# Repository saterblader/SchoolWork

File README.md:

School Work
============
This repository contains projects that I have 
worked on as part of my Masters Degree in 
Computer Engineering while at Syracuse University. 
For Hardware designs provided they are most likely 
laid-out in KiCAD 4.0+ and can be opened with that 
software. All code is provided AS IS and some 
code contains bugs that I never had time to fix 
while working on the project for the class. If 
you are a SU student who has found this please 
note that use of this code for school projects 
is a violation of the University Academic 
Integrity policy and could result in a referral 
to the Academic Integrity Review Board. 

Contact Information
--------------------
Philip D. Geramian 
pdgerami@syr.edu

Last Updated
-------------
April 3rd, 2017

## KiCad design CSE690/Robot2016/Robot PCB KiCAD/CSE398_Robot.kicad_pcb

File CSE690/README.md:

CSE-690
======== 
This folder contains my projects from CSE-690 
Spring 2016 an Independent Study at Syracuse 
University where my advisor for the project 
and I wished to design a new robot platform based 
on the NXP-Freescale Kinetis KL05 Platform. 

If you are a SU student who has found this please 
note that use of this code for school projects 
is a violation of the University Academic 
Integrity policy and could result in a referral 
to the Academic Integrity Review Board. 

Contact Information
--------------------
Philip D. Geramian 
pdgerami@syr.edu

Last Updated
-------------
November 20th, 2016

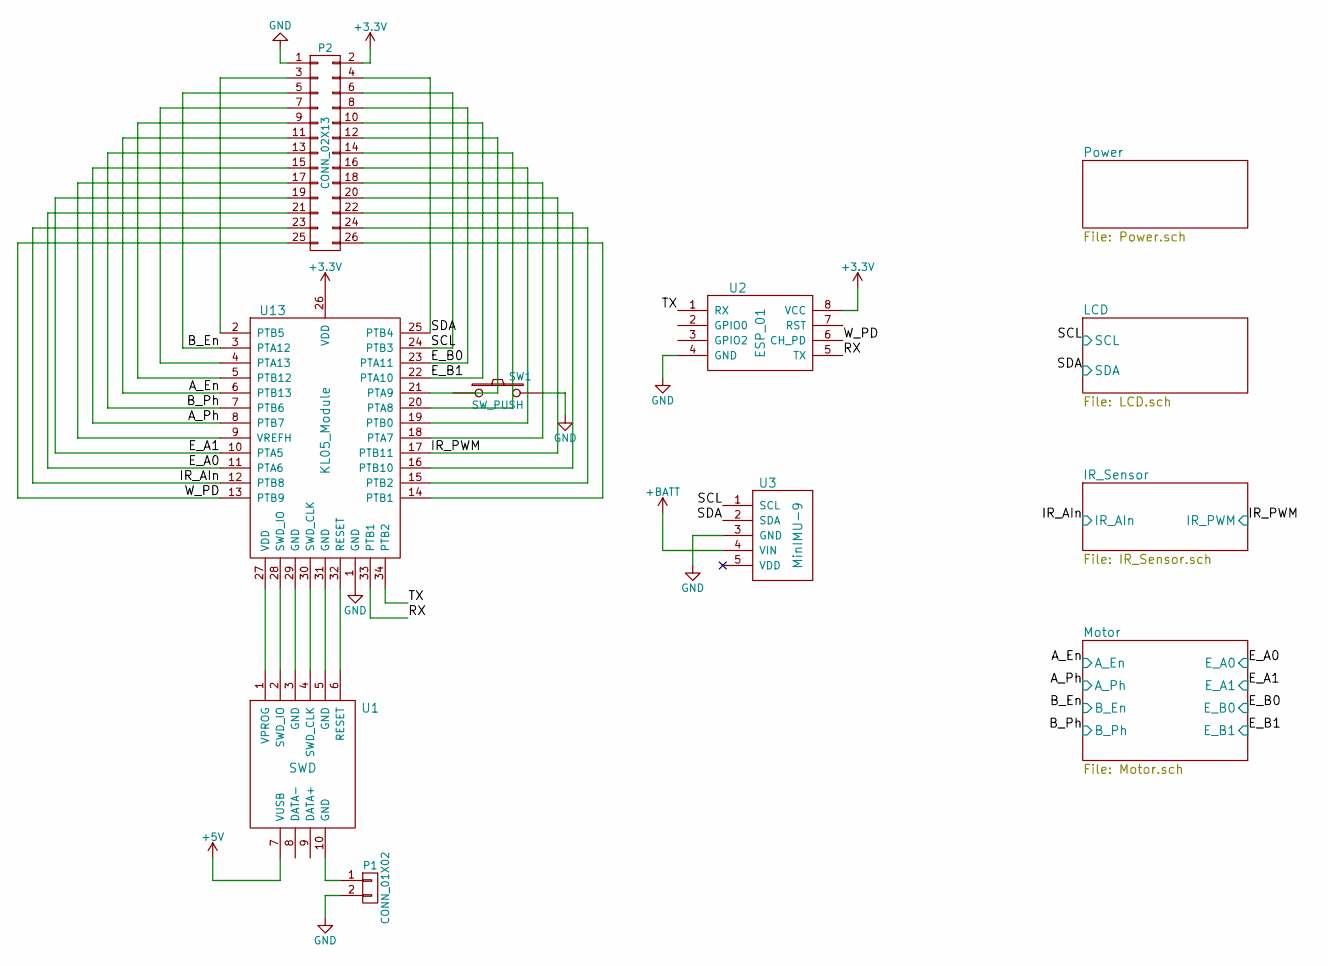
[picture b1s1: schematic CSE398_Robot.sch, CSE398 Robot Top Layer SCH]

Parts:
P1: CONN_01X02; Pin_Header_Straight_1x02
P2: CONN_02X13; Socket_Strip_Straight_2x13
SW1: SW_PUSH; SW_PUSH_SMALL
U1: SWD; GreenBoard_Prog
U2: ESP_01; Pin_Header_Straight_2x04
U3: MinIMU-9; Pin_Header_Straight_1x05
U13: KL05_Module; GreenBoard_uC

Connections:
+3V3: P2.2, U2.8 (VCC), U13.26 (VDD); also elsewhere on the board
+5V: U1.7 (VUSB); also elsewhere on the board
+BATT: U3.4 (VIN); also elsewhere on the board
/IR_Sensor/IR_AIn: P2.23, U13.12 (PTB8); also elsewhere on the board
/IR_Sensor/IR_PWM: P2.20, U13.17 (PTB11); also elsewhere on the board
/LCD/SCL: P2.6, U3.1 (SCL), U13.24 (PTB3); also elsewhere on the board
/LCD/SDA: P2.4, U3.2 (SDA), U13.25 (PTB4); also elsewhere on the board
/Motor/A_En: P2.11, U13.6 (PTB13); also elsewhere on the board
/Motor/A_Ph: P2.15, U13.8 (PTB7); also elsewhere on the board
/Motor/B_En: P2.5, U13.3 (PTA12); also elsewhere on the board
/Motor/B_Ph: P2.13, U13.7 (PTB6); also elsewhere on the board
/Motor/E_A0: P2.21, U13.11 (PTA6); also elsewhere on the board
/Motor/E_A1: P2.19, U13.10 (PTA5); also elsewhere on the board
/Motor/E_B0: P2.8, U13.23 (PTA11); also elsewhere on the board
/Motor/E_B1: P2.10, U13.22 (PTA10); also elsewhere on the board
/RX: U2.5 (TX), U13.33 (PTB1)
/TX: U2.1 (RX), U13.34 (PTB2)
/W_PD: P2.25, U2.6 (CH_PD), U13.13 (PTB9)
GND: P1.2, P2.1, SW1.2, U2.4 (GND), U3.3 (GND), U13.1 (GND); also elsewhere on the board
unnamed: P1.1, U1.10 (GND)
unnamed: P2.3, U13.2 (PTB5)
unnamed: P2.7, U13.4 (PTA13)
unnamed: P2.9, U13.5 (PTB12)
unnamed: P2.12, U13.21 (PTA9)
unnamed: P2.14, U13.20 (PTA8)
unnamed: P2.16, U13.19 (PTB0)
unnamed: P2.17, U13.9 (VREFH)
unnamed: P2.18, U13.18 (PTA7)
unnamed: P2.22, U13.16 (PTB10)
unnamed: P2.24, U13.15 (PTB2)
unnamed: P2.26, U13.14 (PTB1)
unnamed: U1.1 (VPROG), U13.27 (VDD)
unnamed: U1.2 (SWD_IO), U13.28 (SWD_IO)
unnamed: U1.3 (GND), U13.29 (GND)
unnamed: U1.4 (SWD_CLK), U13.30 (SWD_CLK)
unnamed: U1.5 (GND), U13.31 (GND)
unnamed: U1.6 (RESET), U13.32 (RESET)

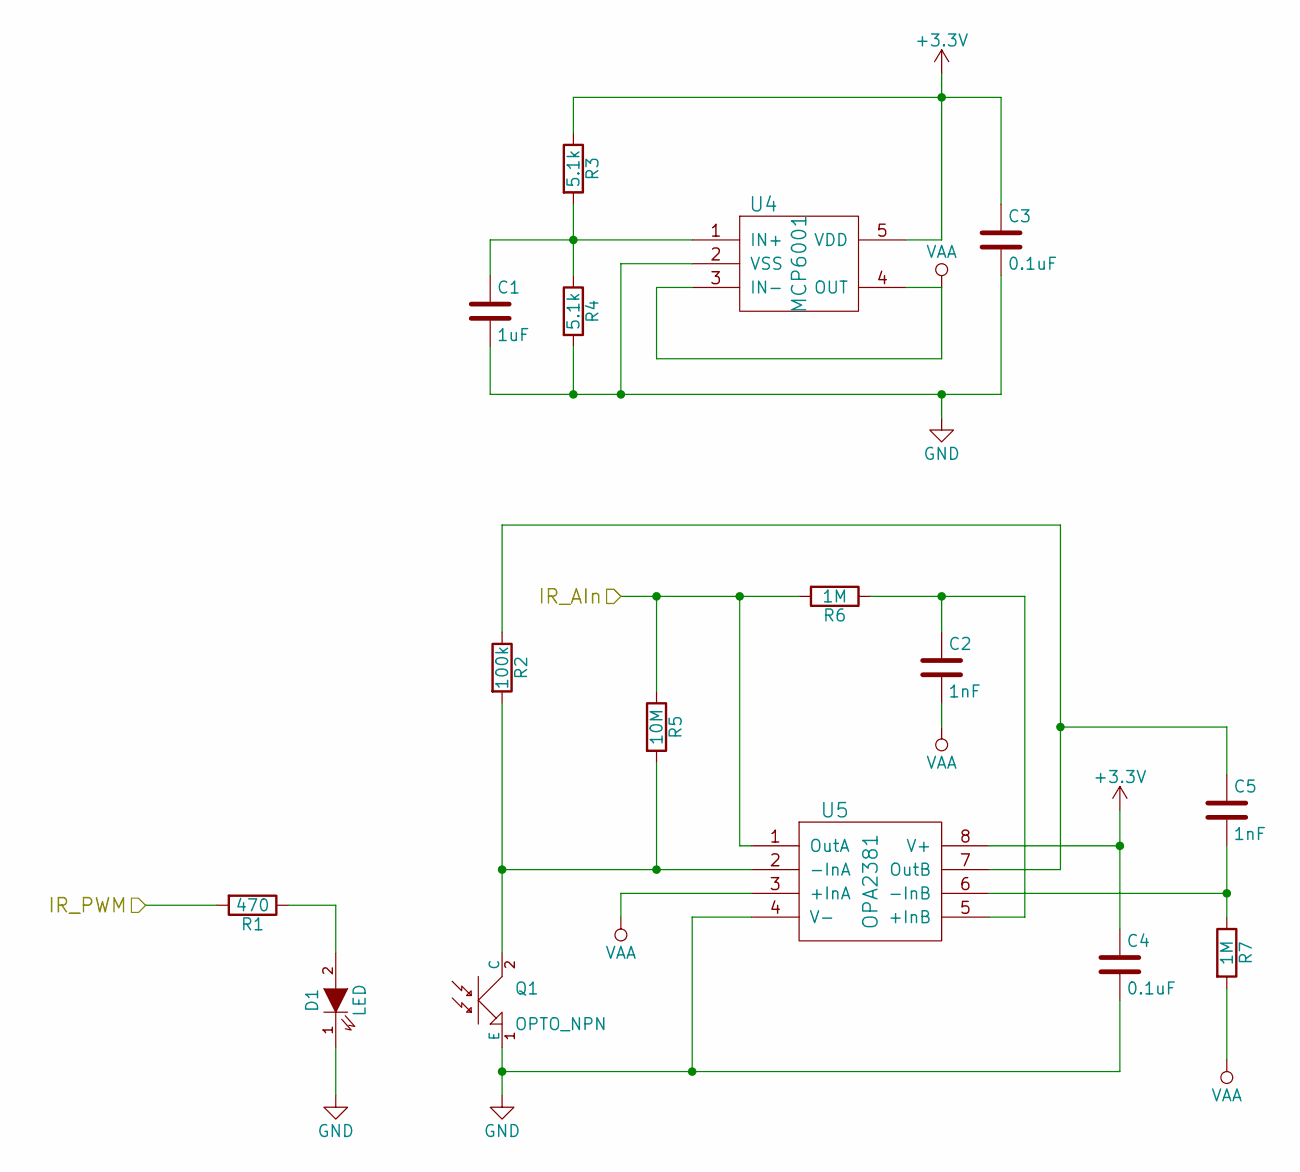
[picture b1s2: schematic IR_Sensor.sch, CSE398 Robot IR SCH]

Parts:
C1: 1uF; C_0805
C2, C5: 1nF; C_0805
C3, C4: 0.1uF; C_0805
D1: LED; 2_SMD_Gull_Wing
Q1: OPTO_NPN; 2_SMD_Gull_Wing
R1: 470; R_0805
R2: 100k; R_0805
R3, R4: 5.1k; R_0805
R5: 10M; R_0805
R6, R7: 1M; R_0805
U4: MCP6001; SOT-23-5
U5: OPA2381; TSSOP-8_3x3mm_Pitch0.65mm

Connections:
+3V3: C3.1, C4.1, R3.1, U4.5 (VDD), U5.8 (V+); also elsewhere on the board
/IR_Sensor/IR_AIn: R5.1, R6.2, U5.1 (OutA); also elsewhere on the board
/IR_Sensor/IR_PWM: R1.2; also elsewhere on the board
GND: C1.2, C3.2, C4.2, D1.1 (K), Q1.1 (E), R4.2, U4.2 (VSS), U5.4 (V-); also elsewhere on the board
unnamed: C1.1, R3.2, R4.1, U4.1 (IN+)
unnamed: C2.1, R6.1, U5.5 (+InB)
unnamed: C5.1, R2.1, U5.7 (OutB)
unnamed: C5.2, R7.1, U5.6 (-InB)
unnamed: D1.2 (A), R1.1
unnamed: Q1.2 (C), R2.2, R5.2, U5.2 (-InA)
VAA: C2.2, R7.2, U4.3 (IN-), U4.4 (OUT), U5.3 (+InA)

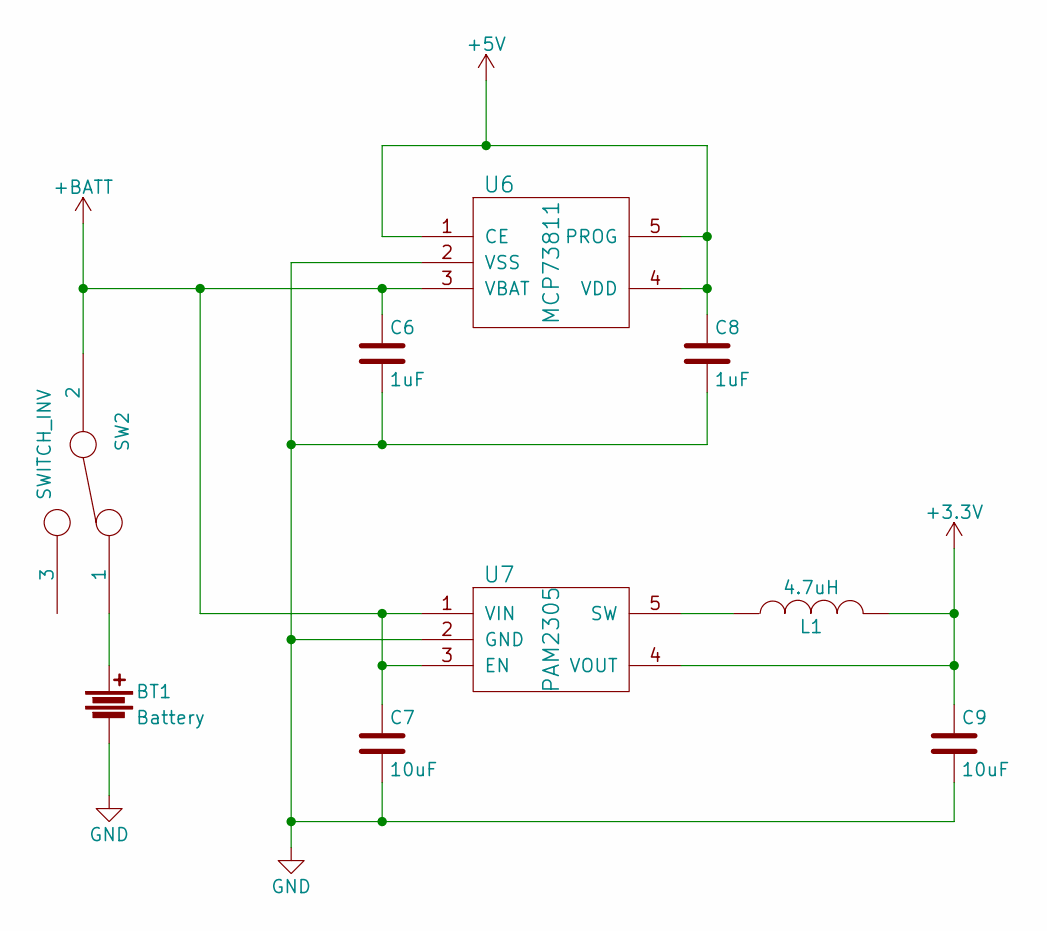
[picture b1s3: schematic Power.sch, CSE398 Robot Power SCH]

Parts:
BT1: Battery; Pin_Header_Straight_1x02
C6, C8: 1uF; C_0805
C7, C9: 10uF; C_0805
L1: 4.7uH; C_0805
SW2: SWITCH_INV; Pin_Header_Straight_1x03
U6: MCP73811; SOT-23-5
U7: PAM2305; SOT-23-5

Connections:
+3V3: C9.1, L1.2, U7.4 (VOUT); also elsewhere on the board
+5V: C8.1, U6.1 (CE), U6.4 (VDD), U6.5 (PROG); also elsewhere on the board
+BATT: C6.1, C7.1, SW2.2, U6.3 (VBAT), U7.1 (VIN), U7.3 (EN); also elsewhere on the board
GND: BT1.2, C6.2, C7.2, C8.2, C9.2, U6.2 (VSS), U7.2 (GND); also elsewhere on the board
unnamed: BT1.1, SW2.1
unnamed: L1.1, U7.5 (SW)

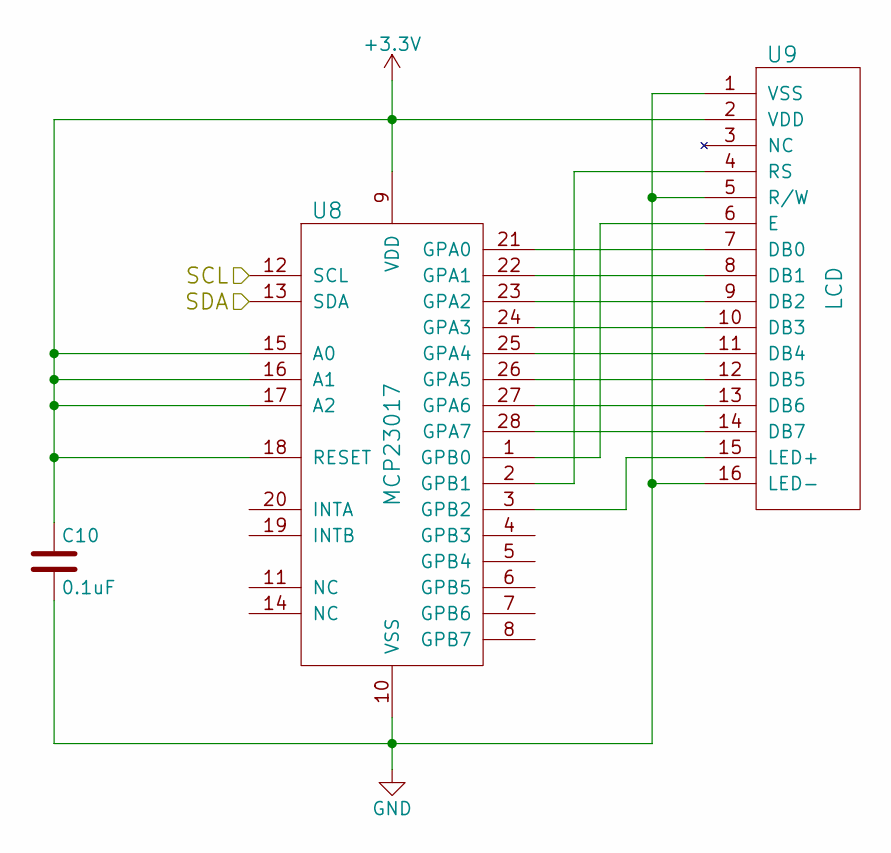
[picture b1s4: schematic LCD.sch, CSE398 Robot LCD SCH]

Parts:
C10: 0.1uF; C_0805
U8: MCP23017; SOIC-28
U9: LCD; Pin_Header_Straight_1x16

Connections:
+3V3: C10.1, U8.9 (VDD), U8.15 (A0), U8.16 (A1), U8.17 (A2), U8.18 (RESET), U9.2 (VDD); also elsewhere on the board
/LCD/SCL: U8.12 (SCL); also elsewhere on the board
/LCD/SDA: U8.13 (SDA); also elsewhere on the board
GND: C10.2, U8.10 (VSS), U9.1 (VSS), U9.5 (R/W), U9.16 (LED-); also elsewhere on the board
unnamed: U8.1 (GPB0), U9.6 (E)
unnamed: U8.2 (GPB1), U9.4 (RS)
unnamed: U8.3 (GPB2), U9.15 (LED+)
unnamed: U8.21 (GPA0), U9.7 (DB0)
unnamed: U8.22 (GPA1), U9.8 (DB1)
unnamed: U8.23 (GPA2), U9.9 (DB2)
unnamed: U8.24 (GPA3), U9.10 (DB3)
unnamed: U8.25 (GPA4), U9.11 (DB4)
unnamed: U8.26 (GPA5), U9.12 (DB5)
unnamed: U8.27 (GPA6), U9.13 (DB6)
unnamed: U8.28 (GPA7), U9.14 (DB7)

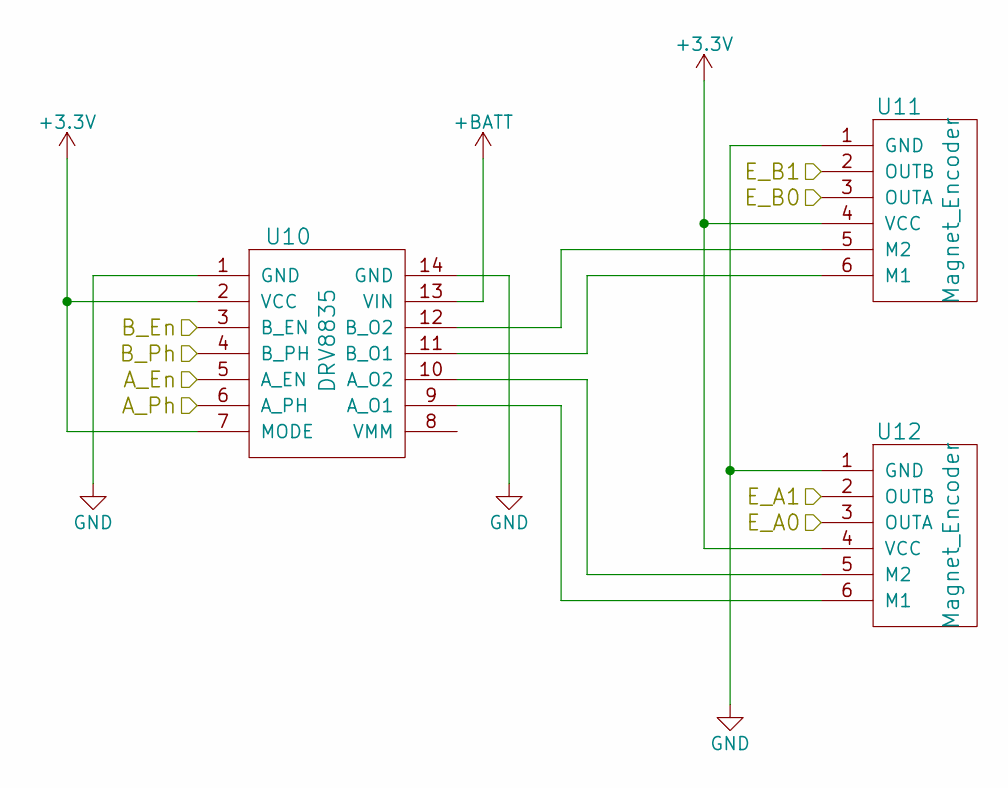
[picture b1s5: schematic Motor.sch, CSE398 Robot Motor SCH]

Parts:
U10: DRV8835
U11, U12: Magnet_Encoder; Pin_Header_Straight_2x03

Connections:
+3V3: U10.2 (VCC), U10.7 (MODE), U11.4 (VCC), U12.4 (VCC); also elsewhere on the board
+BATT: U10.13 (VIN); also elsewhere on the board
/Motor/A_En: U10.5 (A_EN); also elsewhere on the board
/Motor/A_Ph: U10.6 (A_PH); also elsewhere on the board
/Motor/B_En: U10.3 (B_EN); also elsewhere on the board
/Motor/B_Ph: U10.4 (B_PH); also elsewhere on the board
/Motor/E_A0: U12.3 (OUTA); also elsewhere on the board
/Motor/E_A1: U12.2 (OUTB); also elsewhere on the board
/Motor/E_B0: U11.3 (OUTA); also elsewhere on the board
/Motor/E_B1: U11.2 (OUTB); also elsewhere on the board
GND: U10.1 (GND), U10.14 (GND), U11.1 (GND), U12.1 (GND); also elsewhere on the board
unnamed: U10.9 (A_O1), U12.6 (M1)
unnamed: U10.10 (A_O2), U12.5 (M2)
unnamed: U10.11 (B_O1), U11.6 (M1)
unnamed: U10.12 (B_O2), U11.5 (M2)

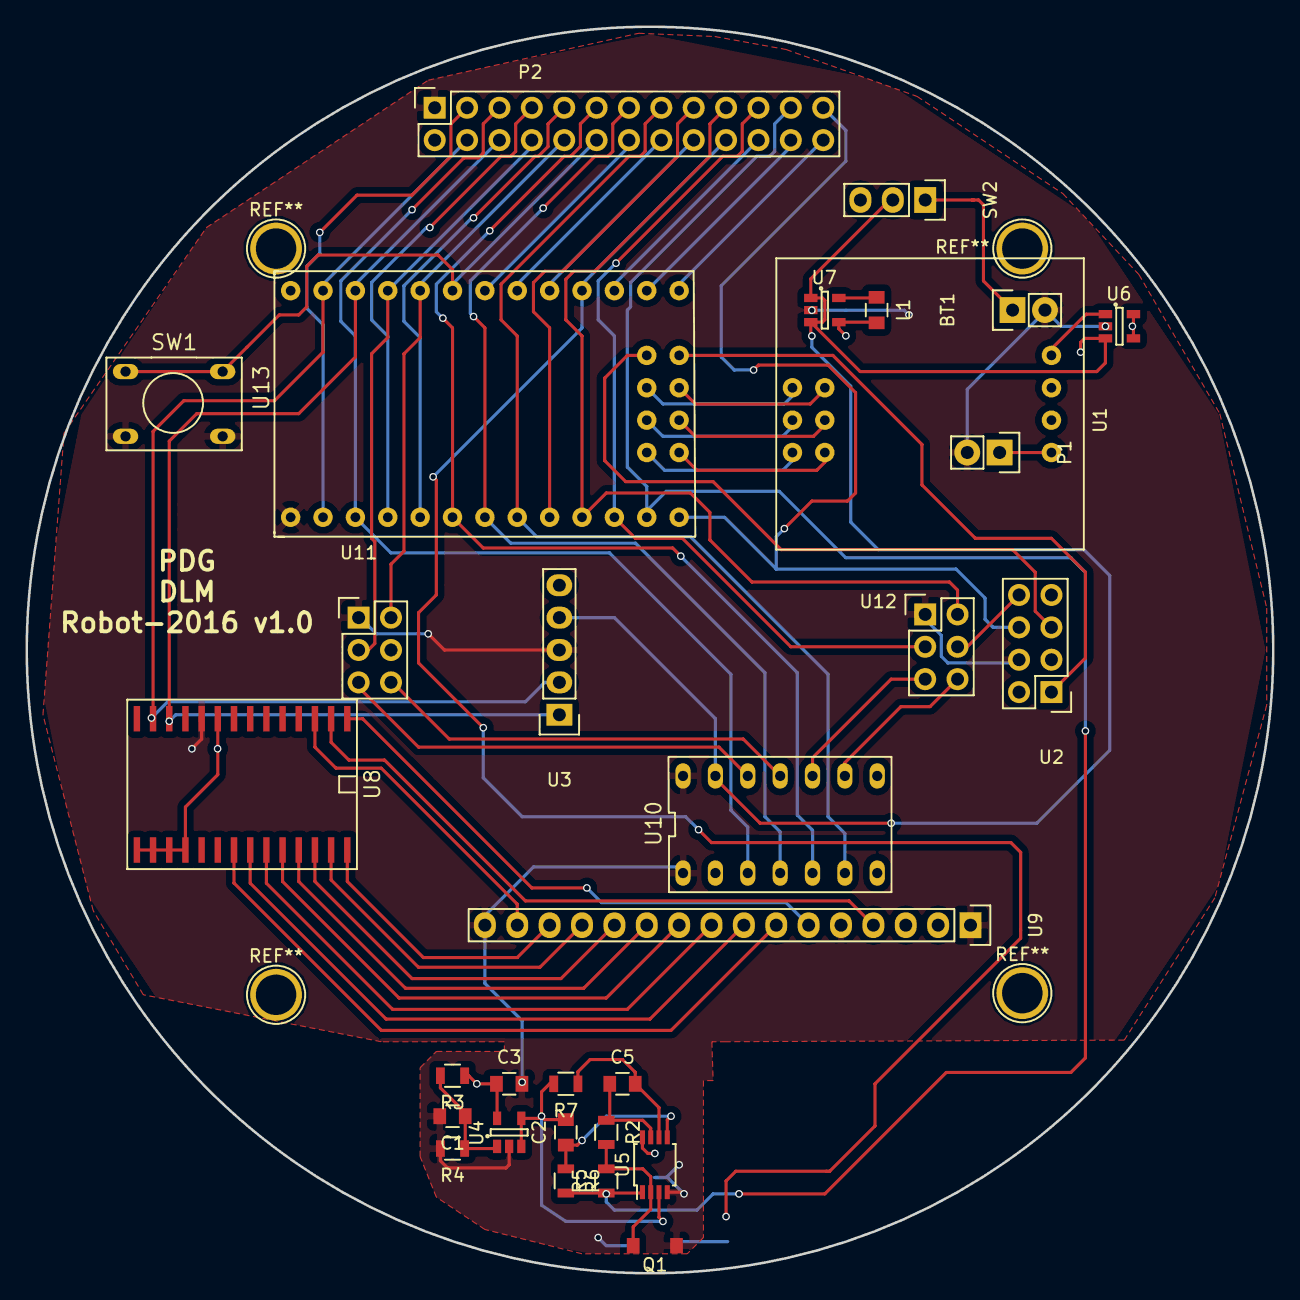
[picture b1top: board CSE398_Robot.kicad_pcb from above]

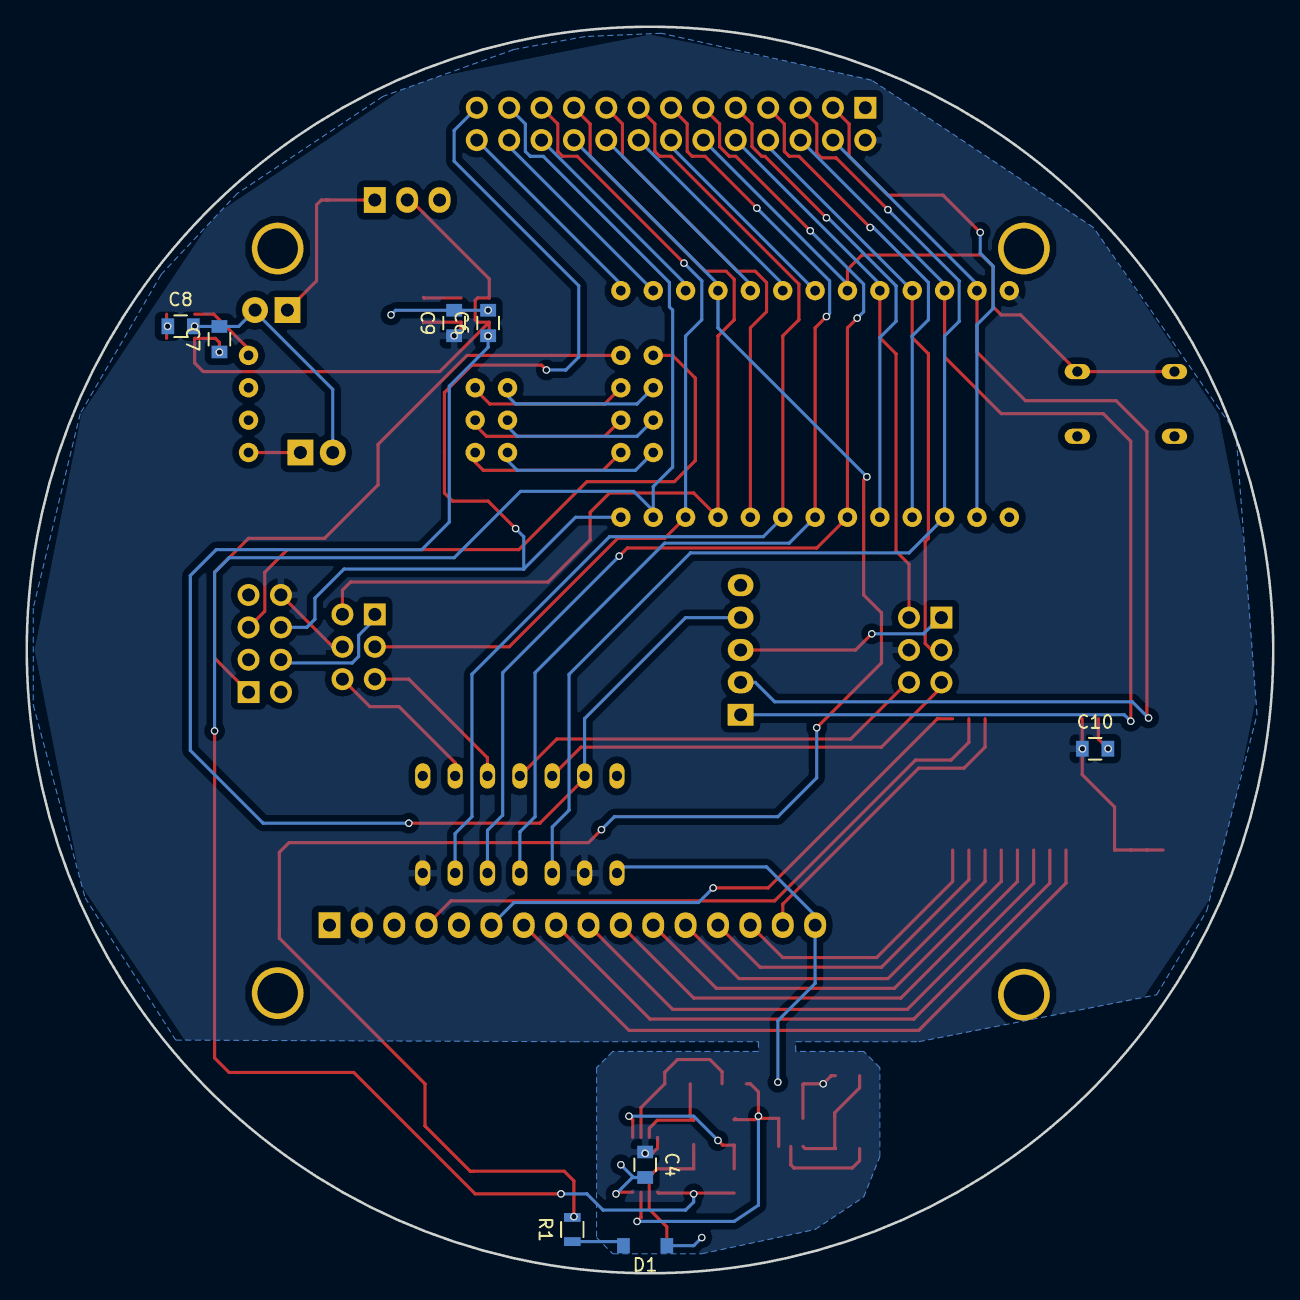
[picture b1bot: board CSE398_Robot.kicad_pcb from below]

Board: 2 copper layers, 97.8 x 97.8 mm, 38 parts (8 on the bottom side), 61 nets.

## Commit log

2016-11-22 Initial Upload
    The Initial Upload of my past school work. 11/21/16
2016-11-22 Fix .gitignore
    Fixed ‘.gitignore’ file
2017-04-04 Added CSE674 coursework
    Added coursework from CSE674 Fall 2016
